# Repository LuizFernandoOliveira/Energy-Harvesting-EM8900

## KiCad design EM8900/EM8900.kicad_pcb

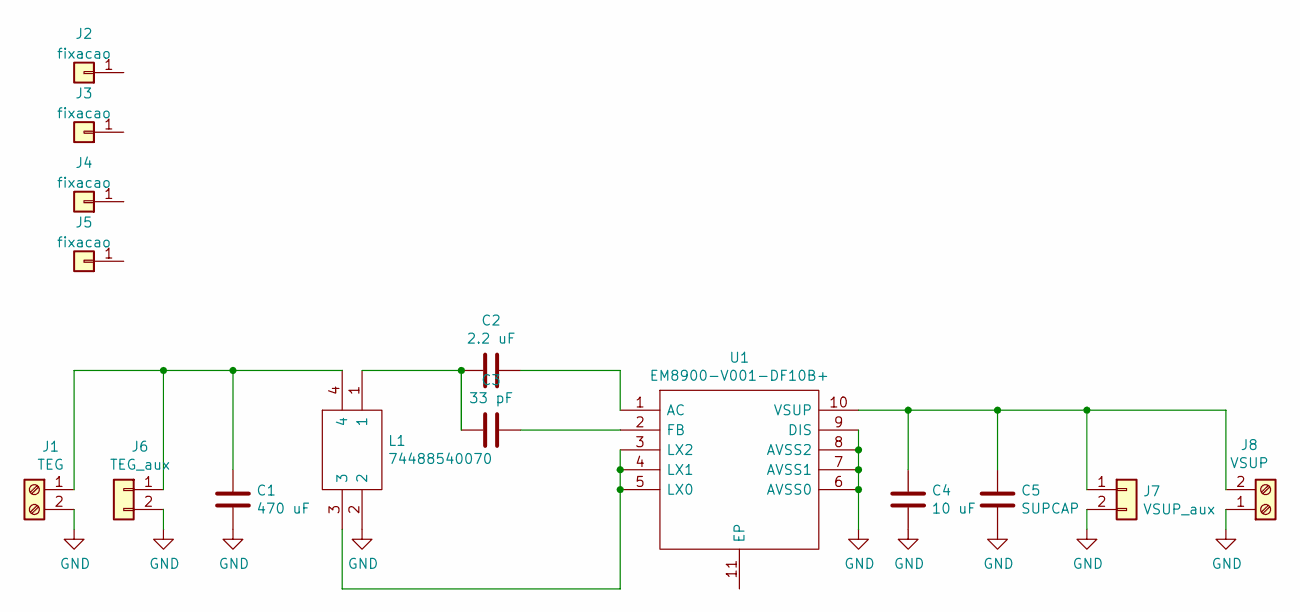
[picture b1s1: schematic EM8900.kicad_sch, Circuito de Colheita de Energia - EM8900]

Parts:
C1: 470 uF; C_0805_2012Metric
C2: 2.2 uF; C_0805_2012Metric
C3: 33 pF; C_0805_2012Metric
C4: 10 uF; C_0805_2012Metric
C5: SUPCAP; CP_Radial_D8.0mm_P5.00mm
J1: TEG; TerminalBlock_Altech_AK300-2_P5.00mm
J2, J3, J4, J5: fixacao; PinHeader_1x01_P2.54mm_Vertical
J6: TEG_aux; PinHeader_1x02_P2.54mm_Vertical
J7: VSUP_aux; PinHeader_1x02_P2.54mm_Vertical
J8: VSUP; TerminalBlock_Altech_AK300-2_P5.00mm
L1: 74488540070; Manufacturer_Part_Number 74488540070; Mouser Part Number 710-74488540070
U1: EM8900-V001-DF10B+; SON50P300X300X90-11N-D; Manufacturer_Part_Number EM8900-V001-DF10B+

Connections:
GND: C1.1, C4.1, C5.2, J1.2, J6.2, J7.2, J8.1, L1.2, U1.6 (AVSS0), U1.7 (AVSS1), U1.8 (AVSS2), U1.9 (DIS)
unnamed: C1.2, J1.1, J6.1, L1.4
unnamed: C2.1, U1.1 (AC)
unnamed: C2.2, C3.2, L1.1
unnamed: C3.1, U1.2 (FB)
unnamed: C4.2, C5.1, J7.1, J8.2, U1.10 (VSUP)
unnamed: L1.3, U1.3 (LX2), U1.4 (LX1), U1.5 (LX0)

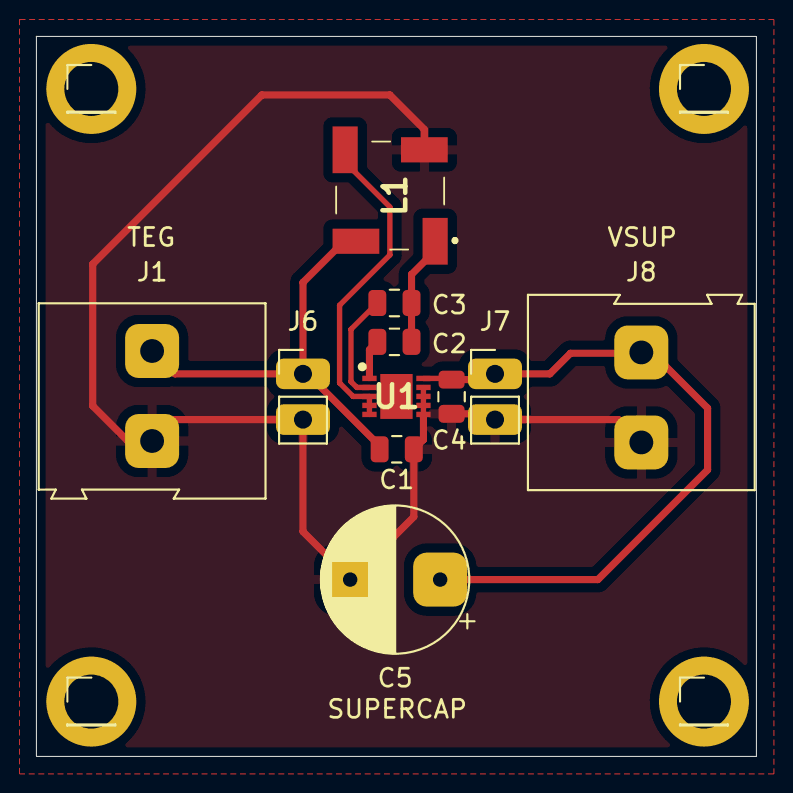
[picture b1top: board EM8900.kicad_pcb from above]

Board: 2 copper layers, 40.0 x 40.0 mm, 15 parts (0 on the bottom side), 7 nets.
